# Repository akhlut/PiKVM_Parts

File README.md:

# PiKVM_Parts

Parts I've made for the PiKVM Project.  https://github.com/pikvm/pikvm

All parts are UNTESTED as of 9/23/2020

The idea behind this is to extend the core PiKVM and turn it into a 4-port switch.  4-Port HDMI switches are ubiquitous and inexpensive, making them a less than ideal candidate for designing a PCB around.  Given that GPIO pins can be assigned to specific functions it only makes sense to start building out a 4-port USB/ATX controller built on top of PiKVM.  Couple this with a way to mimic a button-press on an HDMI switch and we're in business.  

The USB and ATX PCB's stack on top of one another, minimizing the footprint.  The PCB's extend the width of the Pi, but not the length.  At some point I'll have to design a case.

Everything is drawn in EAGLE as it's the tool that I'm used to.

Questions?  
Ask on the discord server:  https://discord.com/channels/580094191938437144

Ask on the subreddit: https://old.reddit.com/r/pikvm/

Happy soldering!

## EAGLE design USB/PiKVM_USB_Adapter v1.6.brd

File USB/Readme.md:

PiKVM USB splitter design notes

AS OF 09232020 THIS DESIGN IS COMPLETE BUT UNTESTED!!!

This design uses Analog Devices ADUM3160 iCouplers to provide galvanic isolation between the OTG USB and the (4) external USB ports.

The GPIO pinout (v1.6) is as follows:

PORT A

    GPIO 17

PORT B

    GPIO 24

PORT C

    GPIO 11

PORT D

    GPIO 13

The OTG port can be switched to Ports A-D by holding GPIO HIGH.  

The OTG port does NOT supply power to the Raspberry Pi!  

Power the Pi by either: 

(1) Use the POWER-IN Port on the PCB to supply 5V to the PCB and Pi via the GPIO header

OR

(2) Use a POE hat to power the PI and use jumper cables to power the PCB @ AUX_PWR header

NEVER USE BOTH POWER OPTIONS AT ONCE!

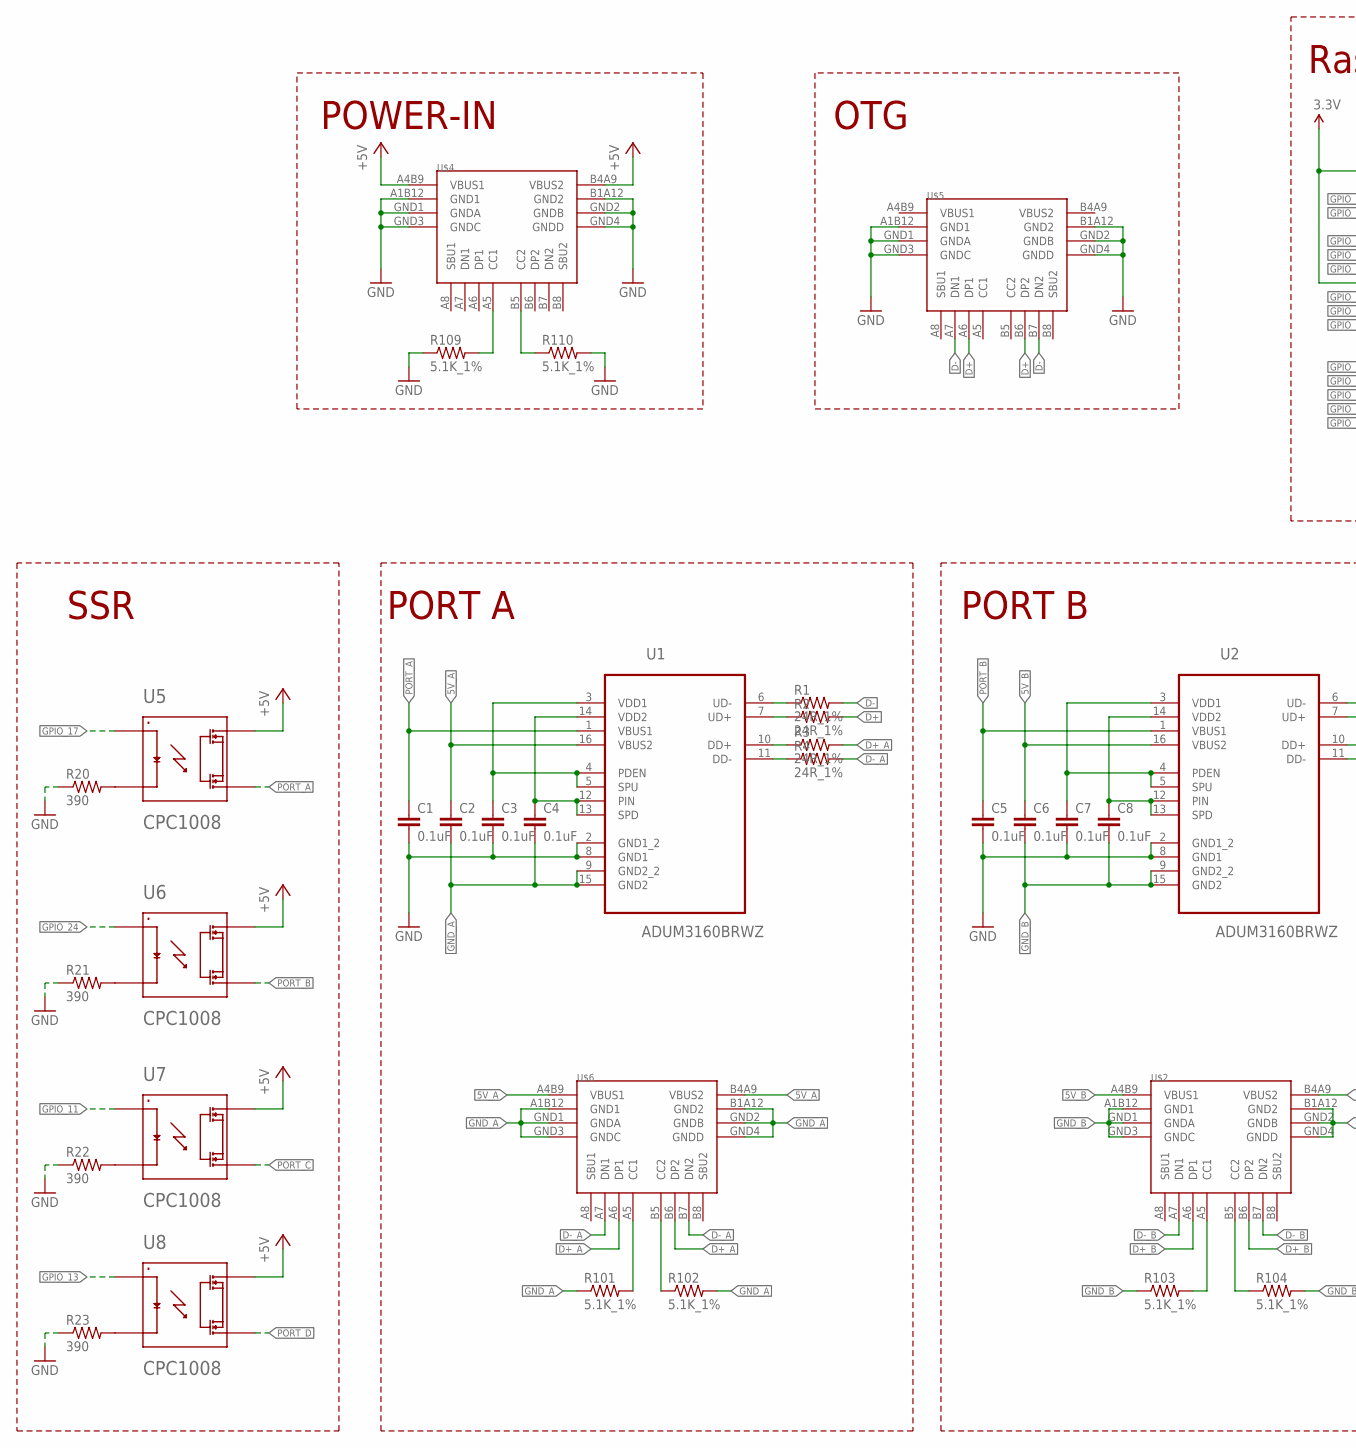
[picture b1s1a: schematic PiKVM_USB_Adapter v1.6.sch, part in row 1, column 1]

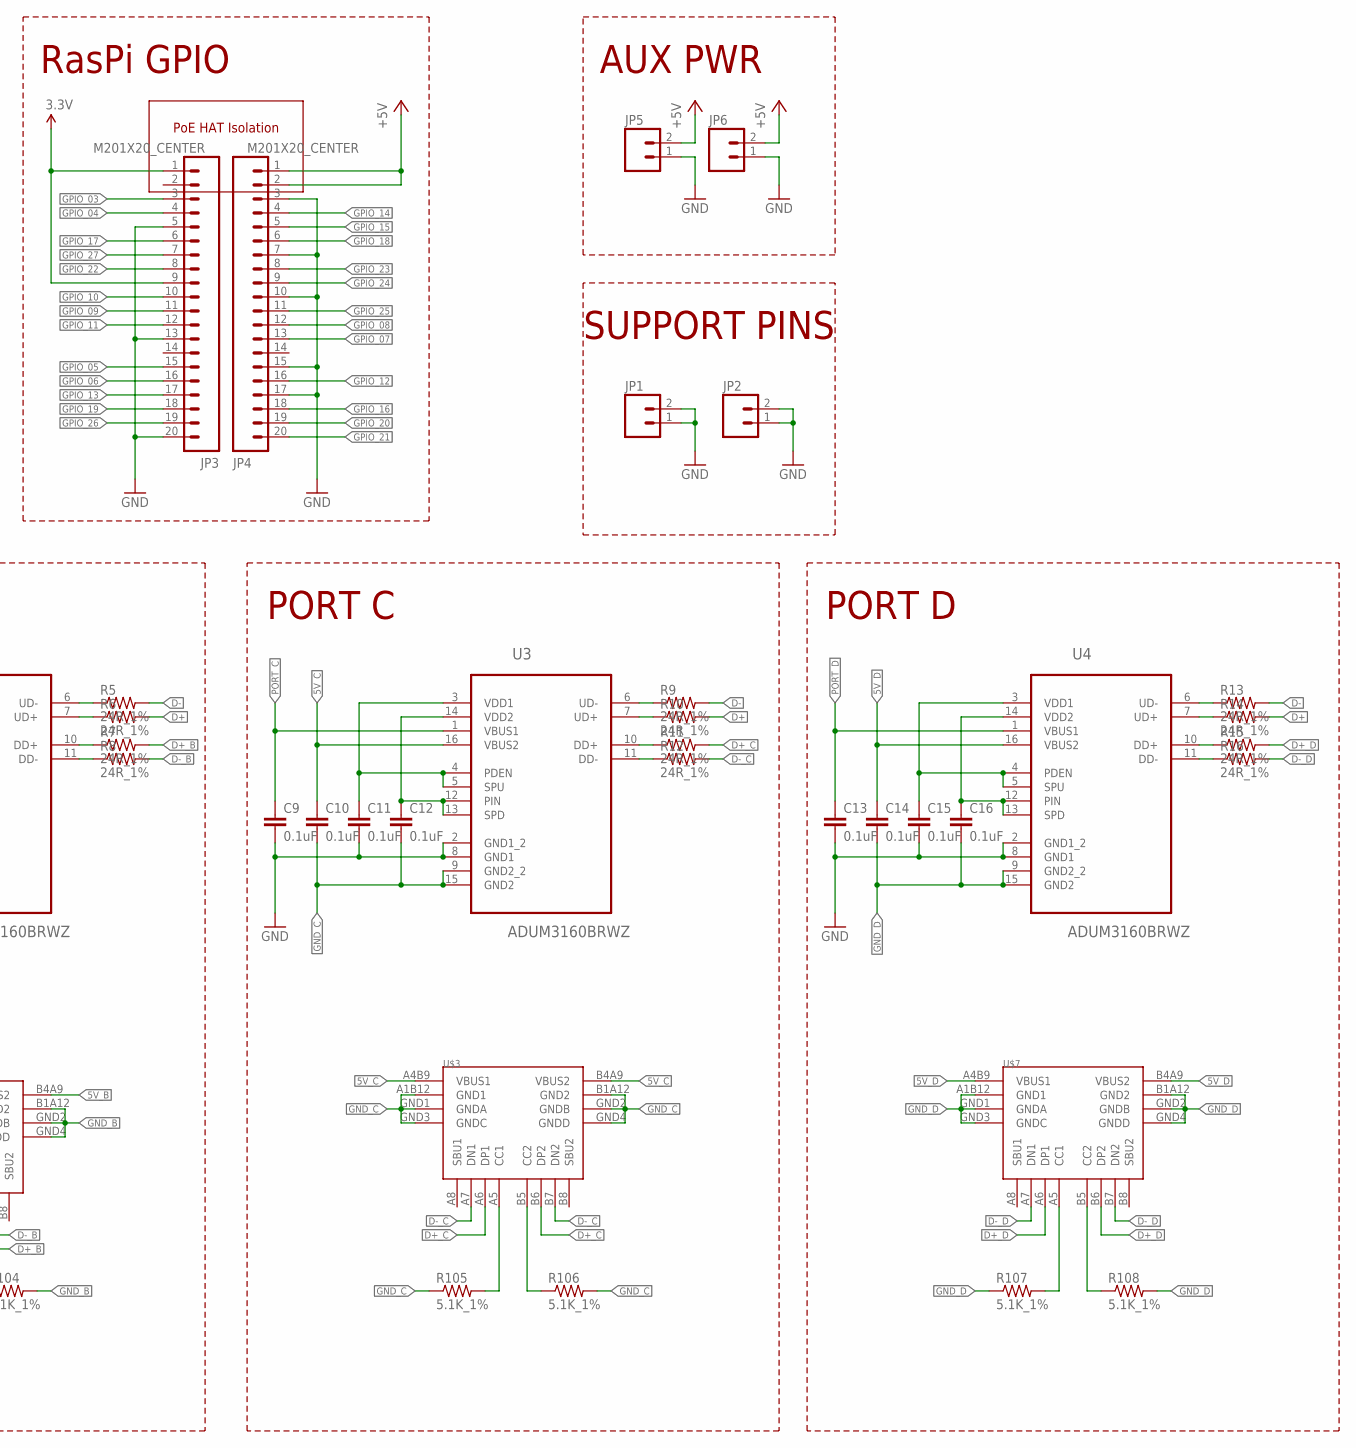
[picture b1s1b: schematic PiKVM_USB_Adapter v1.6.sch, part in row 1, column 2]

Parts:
C1, C2, C3, C4, C5, C6, C7, C8, C9, C10, C11, C12, C13, C14, C15, C16: 0.1uF; 0805
JP1, JP2, JP5, JP6: M02LOCK; 1X02_LOCK
JP3, JP4: M201X20_CENTER; 1X20_CENTER
R1, R2, R3, R4, R5, R6, R7, R8, R9, R10, R11, R12, R13, R14, R15, R16: 24R_1%; 0805
R20, R21, R22, R23: 390; 1206
R101, R102, R103, R104, R105, R106, R107, R108, R109, R110: 5.1K_1%; 0805
U1, U2, U3, U4: ADUM3160BRWZ; SOIC127P1032X265-16N
U5, U6, U7, U8: CPC1008; SOP-4
U$2, U$3, U$4, U$5, U$6, U$7: USB4110GFA; GCT_USB4110GFA

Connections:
3.3V: JP3.1, JP3.9
5V_A: C2.1, U1.16 (VBUS2), U$6.A4B9 (VBUS1), U$6.B4A9 (VBUS2)
5V_B: C6.1, U2.16 (VBUS2), U$2.A4B9 (VBUS1), U$2.B4A9 (VBUS2)
5V_C: C10.1, U3.16 (VBUS2), U$3.A4B9 (VBUS1), U$3.B4A9 (VBUS2)
5V_D: C14.1, U4.16 (VBUS2), U$7.A4B9 (VBUS1), U$7.B4A9 (VBUS2)
+5V: JP4.1, JP4.2, JP5.2, JP6.2, U5.P$4 (4), U6.P$4 (4), U7.P$4 (4), U8.P$4 (4), U$4.A4B9 (VBUS1), U$4.B4A9 (VBUS2)
D+: R2.2, R6.2, R10.2, R14.2, U$5.A6 (DP1), U$5.B6 (DP2)
D+_A: R3.2, U$6.A6 (DP1), U$6.B6 (DP2)
D+_B: R7.2, U$2.A6 (DP1), U$2.B6 (DP2)
D+_C: R11.2, U$3.A6 (DP1), U$3.B6 (DP2)
D+_D: R15.2, U$7.A6 (DP1), U$7.B6 (DP2)
D-: R1.2, R5.2, R9.2, R13.2, U$5.A7 (DN1), U$5.B7 (DN2)
D-_A: R4.2, U$6.A7 (DN1), U$6.B7 (DN2)
D-_B: R8.2, U$2.A7 (DN1), U$2.B7 (DN2)
D-_C: R12.2, U$3.A7 (DN1), U$3.B7 (DN2)
D-_D: R16.2, U$7.A7 (DN1), U$7.B7 (DN2)
GND: C1.2, C3.2, C5.2, C7.2, C9.2, C11.2, C13.2, C15.2, JP1.1, JP1.2, JP2.1, JP2.2, JP3.5, JP3.13, JP3.20, JP4.3, JP4.7, JP4.10, JP4.15, JP4.17, JP5.1, JP6.1, R20.1, R21.1, R22.1, R23.1, R109.1, R110.2, U1.2 (GND1_2), U1.8 (GND1), U2.2 (GND1_2), U2.8 (GND1), U3.2 (GND1_2), U3.8 (GND1), U4.2 (GND1_2), U4.8 (GND1), U$4.A1B12 (GND1), U$4.B1A12 (GND2), U$4.GND1 (GNDA), U$4.GND2 (GNDB), U$4.GND3 (GNDC), U$4.GND4 (GNDD), U$5.A1B12 (GND1), U$5.B1A12 (GND2), U$5.GND1 (GNDA), U$5.GND2 (GNDB), U$5.GND3 (GNDC), U$5.GND4 (GNDD)
GND_A: C2.2, C4.2, R101.1, R102.2, U1.9 (GND2_2), U1.15 (GND2), U$6.A1B12 (GND1), U$6.B1A12 (GND2), U$6.GND1 (GNDA), U$6.GND2 (GNDB), U$6.GND3 (GNDC), U$6.GND4 (GNDD)
GND_B: C6.2, C8.2, R103.1, R104.2, U2.9 (GND2_2), U2.15 (GND2), U$2.A1B12 (GND1), U$2.B1A12 (GND2), U$2.GND1 (GNDA), U$2.GND2 (GNDB), U$2.GND3 (GNDC), U$2.GND4 (GNDD)
GND_C: C10.2, C12.2, R105.1, R106.2, U3.9 (GND2_2), U3.15 (GND2), U$3.A1B12 (GND1), U$3.B1A12 (GND2), U$3.GND1 (GNDA), U$3.GND2 (GNDB), U$3.GND3 (GNDC), U$3.GND4 (GNDD)
GND_D: C14.2, C16.2, R107.1, R108.2, U4.9 (GND2_2), U4.15 (GND2), U$7.A1B12 (GND1), U$7.B1A12 (GND2), U$7.GND1 (GNDA), U$7.GND2 (GNDB), U$7.GND3 (GNDC), U$7.GND4 (GNDD)
GPIO_03: JP3.3
GPIO_04: JP3.4
GPIO_05: JP3.15
GPIO_06: JP3.16
GPIO_07: JP4.13
GPIO_08: JP4.12
GPIO_09: JP3.11
GPIO_10: JP3.10
GPIO_11: JP3.12, U7.P$1 (1)
GPIO_12: JP4.16
GPIO_13: JP3.17, U8.P$1 (1)
GPIO_14: JP4.4
GPIO_15: JP4.5
GPIO_16: JP4.18
GPIO_17: JP3.6, U5.P$1 (1)
GPIO_18: JP4.6
GPIO_19: JP3.18
GPIO_20: JP4.19
GPIO_21: JP4.20
GPIO_22: JP3.8
GPIO_23: JP4.8
GPIO_24: JP4.9, U6.P$1 (1)
GPIO_25: JP4.11
GPIO_26: JP3.19
GPIO_27: JP3.7
unnamed: C8.1, U2.12 (PIN), U2.13 (SPD), U2.14 (VDD2)
unnamed: R5.1, U2.6 (UD-)
unnamed: R6.1, U2.7 (UD+)
unnamed: R7.1, U2.10 (DD+)
unnamed: R20.2, U5.P$2 (2)
unnamed: R8.1, U2.11 (DD-)
unnamed: C3.1, U1.3 (VDD1), U1.4 (PDEN), U1.5 (SPU)
unnamed: R101.2, U$6.A5 (CC1)
unnamed: C12.1, U3.12 (PIN), U3.13 (SPD), U3.14 (VDD2)
unnamed: R9.1, U3.6 (UD-)
unnamed: R10.1, U3.7 (UD+)
unnamed: R11.1, U3.10 (DD+)
unnamed: R12.1, U3.11 (DD-)
unnamed: R102.1, U$6.B5 (CC2)
unnamed: R108.1, U$7.B5 (CC2)
unnamed: C16.1, U4.12 (PIN), U4.13 (SPD), U4.14 (VDD2)
unnamed: R13.1, U4.6 (UD-)
unnamed: R107.2, U$7.A5 (CC1)
unnamed: C4.1, U1.12 (PIN), U1.13 (SPD), U1.14 (VDD2)
unnamed: R14.1, U4.7 (UD+)
unnamed: R15.1, U4.10 (DD+)
unnamed: R16.1, U4.11 (DD-)
unnamed: R1.1, U1.6 (UD-)
unnamed: R2.1, U1.7 (UD+)
unnamed: R3.1, U1.10 (DD+)
unnamed: R4.1, U1.11 (DD-)
unnamed: R105.2, U$3.A5 (CC1)
unnamed: R106.1, U$3.B5 (CC2)
unnamed: R21.2, U6.P$2 (2)
unnamed: R22.2, U7.P$2 (2)
unnamed: R23.2, U8.P$2 (2)
unnamed: C7.1, U2.3 (VDD1), U2.4 (PDEN), U2.5 (SPU)
unnamed: R104.1, U$2.B5 (CC2)
unnamed: C11.1, U3.3 (VDD1), U3.4 (PDEN), U3.5 (SPU)
unnamed: C15.1, U4.3 (VDD1), U4.4 (PDEN), U4.5 (SPU)
unnamed: R103.2, U$2.A5 (CC1)
unnamed: R109.2, U$4.A5 (CC1)
unnamed: R110.1, U$4.B5 (CC2)
PORT_A: C1.1, U1.1 (VBUS1), U5.P$3 (3)
PORT_B: C5.1, U2.1 (VBUS1), U6.P$3 (3)
PORT_C: C9.1, U3.1 (VBUS1), U7.P$3 (3)
PORT_D: C13.1, U4.1 (VBUS1), U8.P$3 (3)
VBUS1: U$5.A4B9 (VBUS1)
VBUS2: U$5.B4A9 (VBUS2)

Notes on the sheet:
PoE HAT Isolation
PORT A
PORT B
PORT C
PORT D
SSR
RasPi GPIO
OTG
POWER-IN
AUX PWR
SUPPORT PINS

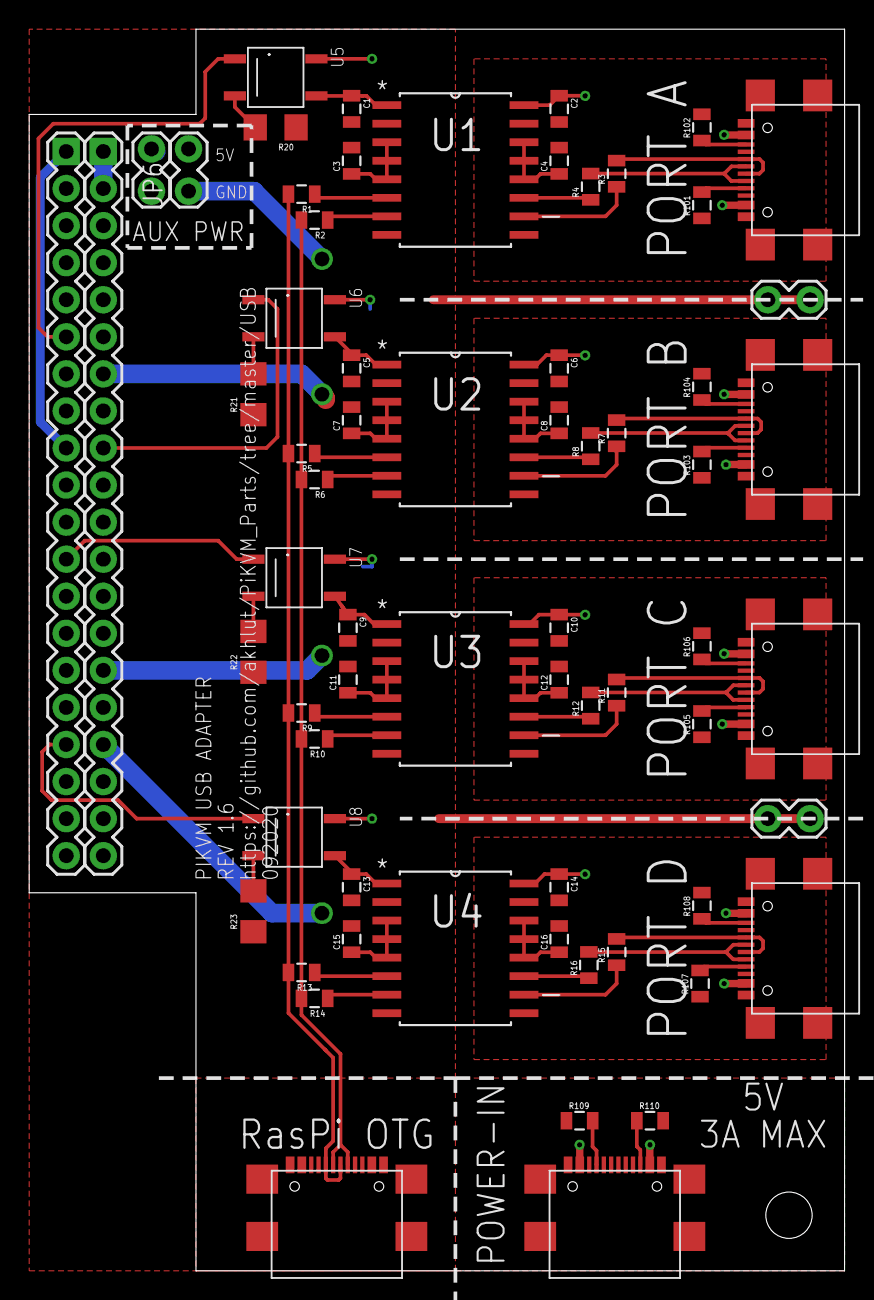
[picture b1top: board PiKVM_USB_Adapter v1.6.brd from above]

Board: 2 copper layers, 55.9 x 85.1 mm, 66 parts (0 on the bottom side), 67 nets.

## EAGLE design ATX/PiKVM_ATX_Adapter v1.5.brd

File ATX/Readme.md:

PiKVM ATX controller design notes

This design uses RJ45 connectors as they are cheap, compact, and ubiquitous.

The RJ45 pinout (v1.5) uses the T-568B pattern and is as follows:

    PIN_1 : W-O : POWER LED +

    PIN_2 : O-W : POWER LED -

    PIN_3 : W-G : IDE LED -

    PIN_4 : Bl-W : RESET -

    PIN_5 : W-Bl : RESET +

    PIN_6 : G-W : IDE LED +

    PIN_7 : W-Br : POWER +

    PIN_8 : Br-W : POWER -

-----

The GPIO pinout (v1) is as follows:

PORT A

    GPIO 03 - POWER

    GPIO 15 - RESET

    GPIO 04 - POWER LED

    GPIO 14 - IDE LED

PORT B

    GPIO 18 - POWER

    GPIO 27 - RESET

    GPIO 22 - POWER LED

    GPIO 23 - IDE LED

PORT C

    GPIO 10 - POWER

    GPIO 08 - RESET

    GPIO 09 - POWER LED

    GPIO 25 - IDE LED

PORT D

    GPIO 07 - POWER

    GPIO 06 - RESET

    GPIO 12 - POWER LED

    GPIO 05 - IDE LED

---

There is also a port to control an external switch.  A DC barrel jack is provided for connectivity.  There is no polarity, simply Common/Normally Open.  This is useful to control external HDMI/KVM switches.

EXTERNAL CONTROL PORT - GPIO 21

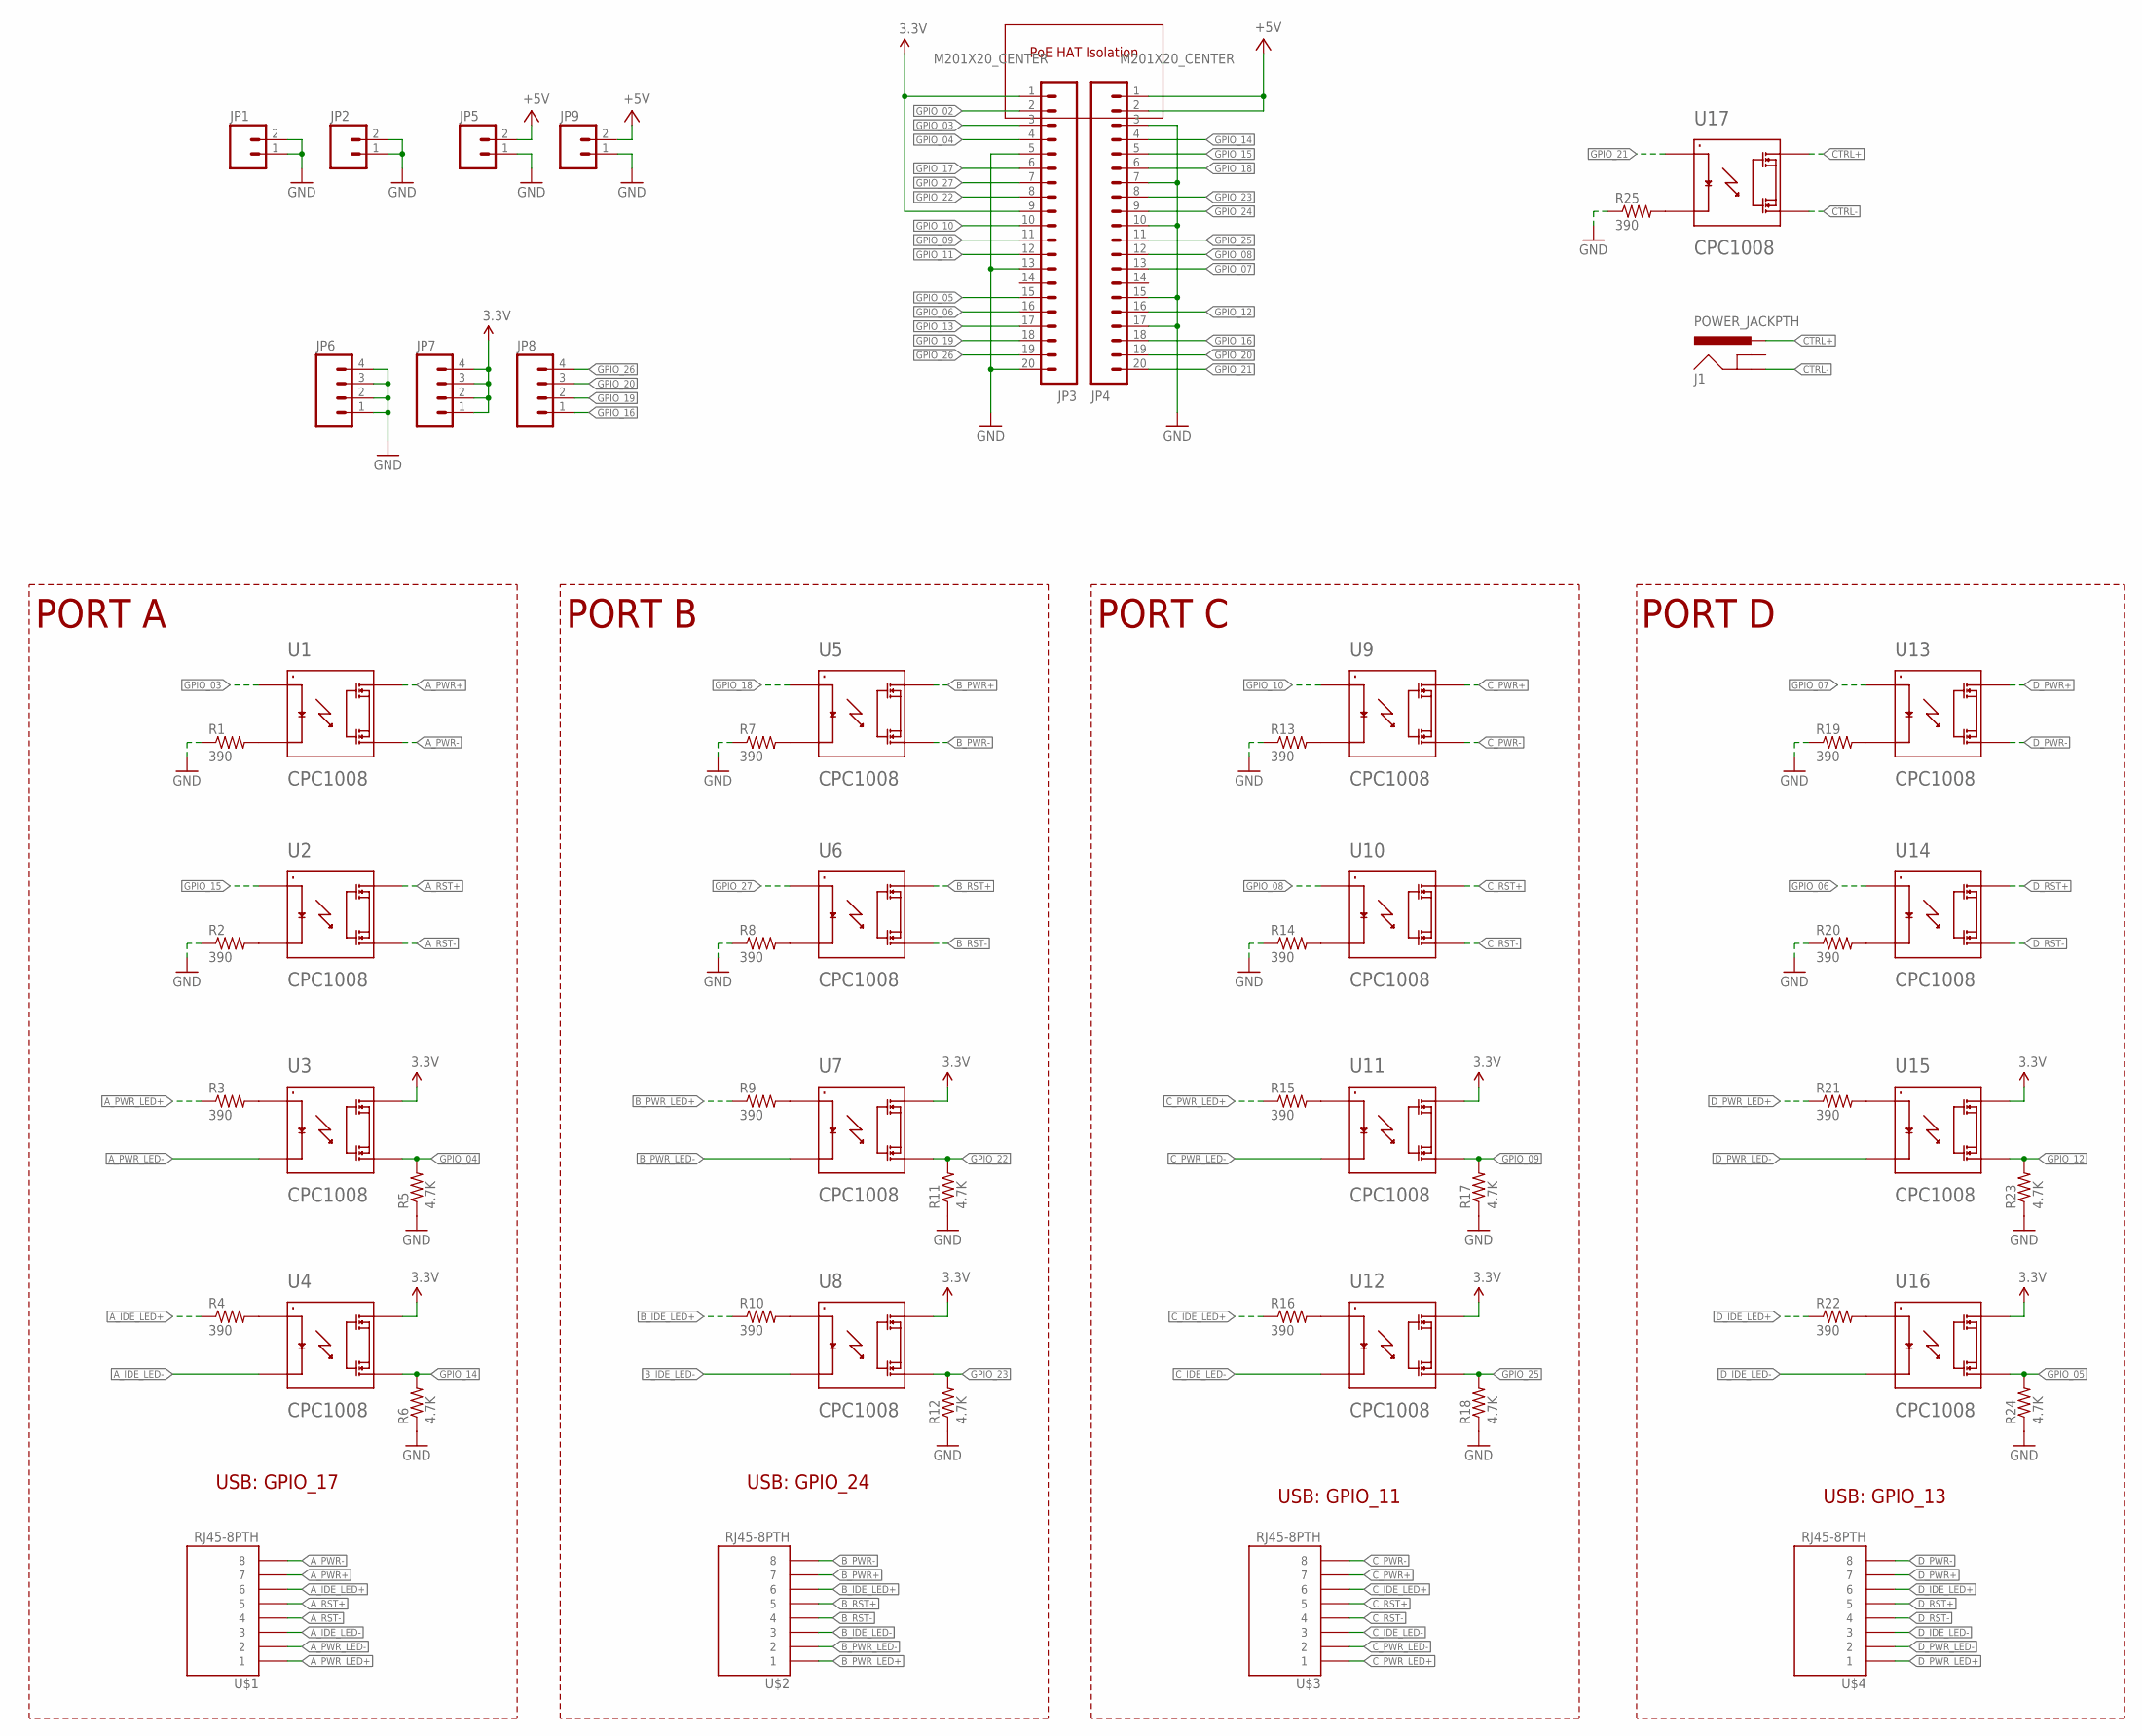
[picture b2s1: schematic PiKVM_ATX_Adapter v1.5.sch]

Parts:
J1: POWER_JACKPTH; POWER_JACK_PTH
JP1, JP2, JP5, JP9: M02LOCK; 1X02_LOCK
JP3, JP4: M201X20_CENTER; 1X20_CENTER
JP6, JP7, JP8: M04PTH; 1X04
R1, R2, R3, R4, R7, R8, R9, R10, R13, R14, R15, R16, R19, R20, R21, R22, R25: 390; 1206
R5, R6, R11, R12, R17, R18, R23, R24: 4.7K; 1206
U1, U2, U3, U4, U5, U6, U7, U8, U9, U10, U11, U12, U13, U14, U15, U16, U17: CPC1008; SOP-4
U$1, U$2, U$3, U$4: RJ45-8PTH; RJ45-8

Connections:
3.3V: JP3.1, JP3.9, JP7.1, JP7.2, JP7.3, JP7.4, U3.P$4 (4), U4.P$4 (4), U7.P$4 (4), U8.P$4 (4), U11.P$4 (4), U12.P$4 (4), U15.P$4 (4), U16.P$4 (4)
+5V: JP4.1, JP4.2, JP5.2, JP9.2
A_IDE_LED+: R4.1, U$1.6
A_IDE_LED-: U4.P$2 (2), U$1.3
A_PWR+: U1.P$4 (4), U$1.7
A_PWR-: U1.P$3 (3), U$1.8
A_PWR_LED+: R3.1, U$1.1
A_PWR_LED-: U3.P$2 (2), U$1.2
A_RST+: U2.P$4 (4), U$1.5
A_RST-: U2.P$3 (3), U$1.4
B_IDE_LED+: R10.1, U$2.6
B_IDE_LED-: U8.P$2 (2), U$2.3
B_PWR+: U5.P$4 (4), U$2.7
B_PWR-: U5.P$3 (3), U$2.8
B_PWR_LED+: R9.1, U$2.1
B_PWR_LED-: U7.P$2 (2), U$2.2
B_RST+: U6.P$4 (4), U$2.5
B_RST-: U6.P$3 (3), U$2.4
CTRL+: J1.PWR, U17.P$4 (4)
CTRL-: J1.GND, U17.P$3 (3)
C_IDE_LED+: R16.1, U$3.6
C_IDE_LED-: U12.P$2 (2), U$3.3
C_PWR+: U9.P$4 (4), U$3.7
C_PWR-: U9.P$3 (3), U$3.8
C_PWR_LED+: R15.1, U$3.1
C_PWR_LED-: U11.P$2 (2), U$3.2
C_RST+: U10.P$4 (4), U$3.5
C_RST-: U10.P$3 (3), U$3.4
D_IDE_LED+: R22.1, U$4.6
D_IDE_LED-: U16.P$2 (2), U$4.3
D_PWR+: U13.P$4 (4), U$4.7
D_PWR-: U13.P$3 (3), U$4.8
D_PWR_LED+: R21.1, U$4.1
D_PWR_LED-: U15.P$2 (2), U$4.2
D_RST+: U14.P$4 (4), U$4.5
D_RST-: U14.P$3 (3), U$4.4
GND: JP1.1, JP1.2, JP2.1, JP2.2, JP3.5, JP3.13, JP3.20, JP4.3, JP4.7, JP4.10, JP4.15, JP4.17, JP5.1, JP6.1, JP6.2, JP6.3, JP6.4, JP9.1, R1.1, R2.1, R5.1, R6.1, R7.1, R8.1, R11.1, R12.1, R13.1, R14.1, R17.1, R18.1, R19.1, R20.1, R23.1, R24.1, R25.1
GPIO_02: JP3.2
GPIO_03: JP3.3, U1.P$1 (1)
GPIO_04: JP3.4, R5.2, U3.P$3 (3)
GPIO_05: JP3.15, R24.2, U16.P$3 (3)
GPIO_06: JP3.16, U14.P$1 (1)
GPIO_07: JP4.13, U13.P$1 (1)
GPIO_08: JP4.12, U10.P$1 (1)
GPIO_09: JP3.11, R17.2, U11.P$3 (3)
GPIO_10: JP3.10, U9.P$1 (1)
GPIO_11: JP3.12
GPIO_12: JP4.16, R23.2, U15.P$3 (3)
GPIO_13: JP3.17
GPIO_14: JP4.4, R6.2, U4.P$3 (3)
GPIO_15: JP4.5, U2.P$1 (1)
GPIO_16: JP4.18, JP8.1
GPIO_17: JP3.6
GPIO_18: JP4.6, U5.P$1 (1)
GPIO_19: JP3.18, JP8.2
GPIO_20: JP4.19, JP8.3
GPIO_21: JP4.20, U17.P$1 (1)
GPIO_22: JP3.8, R11.2, U7.P$3 (3)
GPIO_23: JP4.8, R12.2, U8.P$3 (3)
GPIO_24: JP4.9
GPIO_25: JP4.11, R18.2, U12.P$3 (3)
GPIO_26: JP3.19, JP8.4
GPIO_27: JP3.7, U6.P$1 (1)
unnamed: R2.2, U2.P$2 (2)
unnamed: R3.2, U3.P$1 (1)
unnamed: R7.2, U5.P$2 (2)
unnamed: R1.2, U1.P$2 (2)
unnamed: R4.2, U4.P$1 (1)
unnamed: R8.2, U6.P$2 (2)
unnamed: R9.2, U7.P$1 (1)
unnamed: R10.2, U8.P$1 (1)
unnamed: R13.2, U9.P$2 (2)
unnamed: R14.2, U10.P$2 (2)
unnamed: R15.2, U11.P$1 (1)
unnamed: R16.2, U12.P$1 (1)
unnamed: R19.2, U13.P$2 (2)
unnamed: R20.2, U14.P$2 (2)
unnamed: R21.2, U15.P$1 (1)
unnamed: R22.2, U16.P$1 (1)
unnamed: R25.2, U17.P$2 (2)

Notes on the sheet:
PoE HAT Isolation
PORT A
PORT B
PORT C
PORT D
USB: GPIO_17
USB: GPIO_24
USB: GPIO_11
USB: GPIO_13

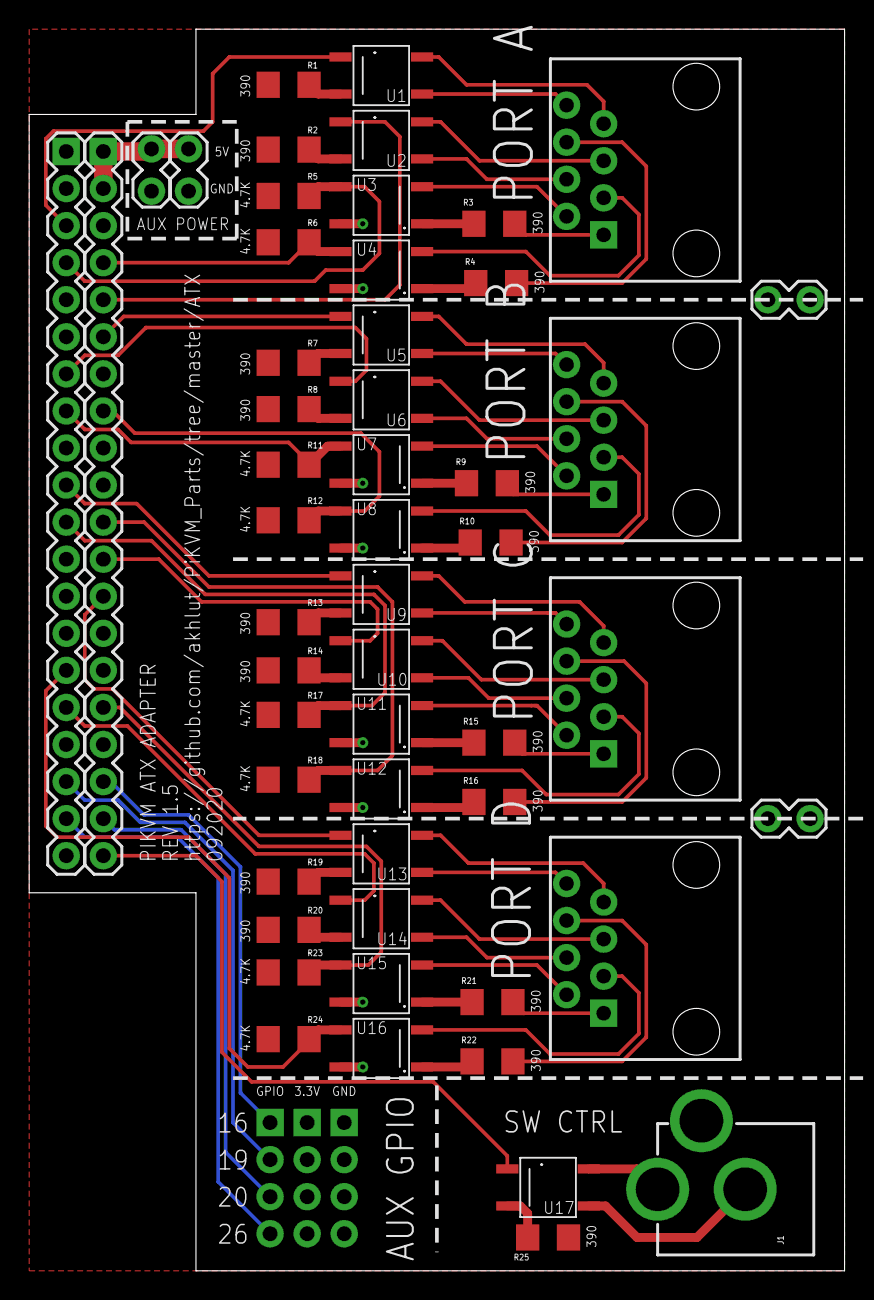
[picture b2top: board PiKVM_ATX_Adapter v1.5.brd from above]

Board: 2 copper layers, 55.9 x 85.1 mm, 56 parts (0 on the bottom side), 75 nets.

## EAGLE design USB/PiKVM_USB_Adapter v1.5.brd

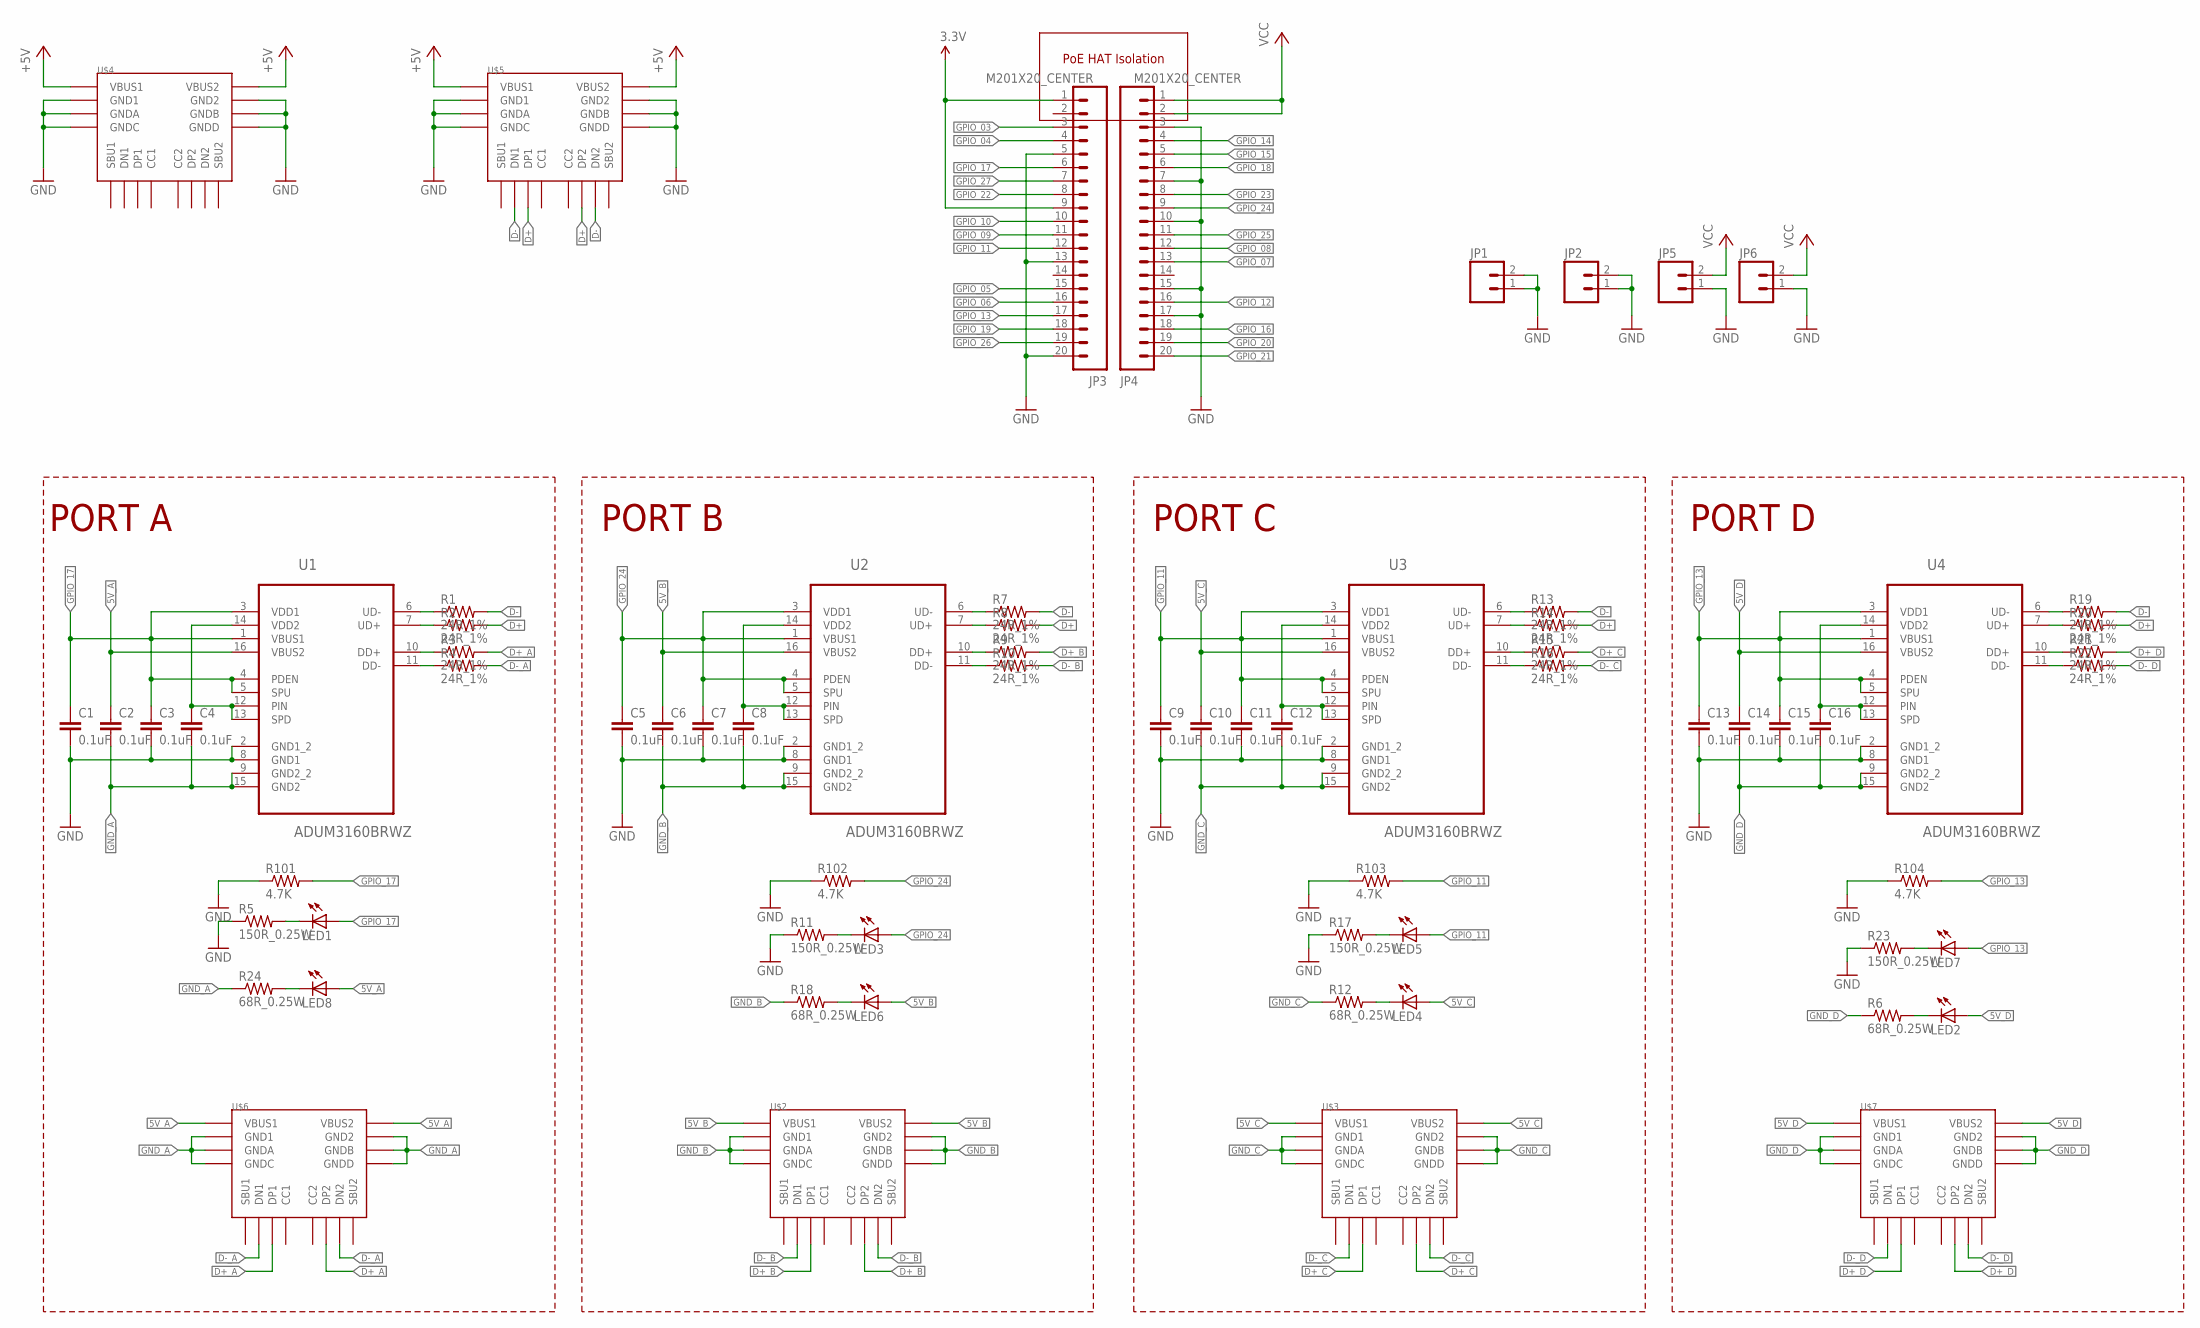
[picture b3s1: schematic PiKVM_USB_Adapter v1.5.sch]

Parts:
C1, C2, C3, C4, C5, C6, C7, C8, C9, C10, C11, C12, C13, C14, C15, C16: 0.1uF; 0805
JP1, JP2, JP5, JP6: M02LOCK; 1X02_LOCK
JP3, JP4: M201X20_CENTER; 1X20_CENTER
LED1, LED2, LED3, LED4, LED5, LED6, LED7, LED8: LED1206; LED-1206
R1, R2, R3, R4, R7, R8, R9, R10, R13, R14, R15, R16, R19, R20, R21, R22: 24R_1%; 0805
R5, R11, R17, R23: 150R_0.25W; 1206
R6, R12, R18, R24: 68R_0.25W; 1206
R101, R102, R103, R104: 4.7K; 1206
U1, U2, U3, U4: ADUM3160BRWZ; SOIC127P1032X265-16N
U$2, U$3, U$4, U$5, U$6, U$7: USB4110GFA; GCT_USB4110GFA

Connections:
3.3V: JP3.1, JP3.9
5V_A: C2.1, LED8.A, U1.16 (VBUS2), U$6.A4B9 (VBUS1), U$6.B4A9 (VBUS2)
5V_B: C6.1, LED6.A, U2.16 (VBUS2), U$2.A4B9 (VBUS1), U$2.B4A9 (VBUS2)
5V_C: C10.1, LED4.A, U3.16 (VBUS2), U$3.A4B9 (VBUS1), U$3.B4A9 (VBUS2)
5V_D: C14.1, LED2.A, U4.16 (VBUS2), U$7.A4B9 (VBUS1), U$7.B4A9 (VBUS2)
+5V: U$4.A4B9 (VBUS1), U$4.B4A9 (VBUS2), U$5.A4B9 (VBUS1), U$5.B4A9 (VBUS2)
D+: R2.2, R8.2, R14.2, R20.2, U$5.A6 (DP1), U$5.B6 (DP2)
D+_A: R3.2, U$6.A6 (DP1), U$6.B6 (DP2)
D+_B: R9.2, U$2.A6 (DP1), U$2.B6 (DP2)
D+_C: R15.2, U$3.A6 (DP1), U$3.B6 (DP2)
D+_D: R21.2, U$7.A6 (DP1), U$7.B6 (DP2)
D-: R1.2, R7.2, R13.2, R19.2, U$5.A7 (DN1), U$5.B7 (DN2)
D-_A: R4.2, U$6.A7 (DN1), U$6.B7 (DN2)
D-_B: R10.2, U$2.A7 (DN1), U$2.B7 (DN2)
D-_C: R16.2, U$3.A7 (DN1), U$3.B7 (DN2)
D-_D: R22.2, U$7.A7 (DN1), U$7.B7 (DN2)
GND: C1.2, C3.2, C5.2, C7.2, C9.2, C11.2, C13.2, C15.2, JP1.1, JP1.2, JP2.1, JP2.2, JP3.5, JP3.13, JP3.20, JP4.3, JP4.7, JP4.10, JP4.15, JP4.17, JP5.1, JP6.1, R5.1, R11.1, R17.1, R23.1, R101.1, R102.1, R103.1, R104.1, U1.2 (GND1_2), U1.8 (GND1), U2.2 (GND1_2), U2.8 (GND1), U3.2 (GND1_2), U3.8 (GND1), U4.2 (GND1_2), U4.8 (GND1), U$4.A1B12 (GND1), U$4.B1A12 (GND2), U$4.GND1 (GNDA), U$4.GND2 (GNDB), U$4.GND3 (GNDC), U$4.GND4 (GNDD), U$5.A1B12 (GND1), U$5.B1A12 (GND2), U$5.GND1 (GNDA), U$5.GND2 (GNDB), U$5.GND3 (GNDC), U$5.GND4 (GNDD)
GND_A: C2.2, C4.2, R24.1, U1.9 (GND2_2), U1.15 (GND2), U$6.A1B12 (GND1), U$6.B1A12 (GND2), U$6.GND1 (GNDA), U$6.GND2 (GNDB), U$6.GND3 (GNDC), U$6.GND4 (GNDD)
GND_B: C6.2, C8.2, R18.1, U2.9 (GND2_2), U2.15 (GND2), U$2.A1B12 (GND1), U$2.B1A12 (GND2), U$2.GND1 (GNDA), U$2.GND2 (GNDB), U$2.GND3 (GNDC), U$2.GND4 (GNDD)
GND_C: C10.2, C12.2, R12.1, U3.9 (GND2_2), U3.15 (GND2), U$3.A1B12 (GND1), U$3.B1A12 (GND2), U$3.GND1 (GNDA), U$3.GND2 (GNDB), U$3.GND3 (GNDC), U$3.GND4 (GNDD)
GND_D: C14.2, C16.2, R6.1, U4.9 (GND2_2), U4.15 (GND2), U$7.A1B12 (GND1), U$7.B1A12 (GND2), U$7.GND1 (GNDA), U$7.GND2 (GNDB), U$7.GND3 (GNDC), U$7.GND4 (GNDD)
GPIO_03: JP3.3
GPIO_04: JP3.4
GPIO_05: JP3.15
GPIO_06: JP3.16
GPIO_07: JP4.13
GPIO_08: JP4.12
GPIO_09: JP3.11
GPIO_10: JP3.10
GPIO_11: C9.1, C11.1, JP3.12, LED5.A, R103.2, U3.1 (VBUS1), U3.3 (VDD1), U3.4 (PDEN), U3.5 (SPU)
GPIO_12: JP4.16
GPIO_13: C13.1, C15.1, JP3.17, LED7.A, R104.2, U4.1 (VBUS1), U4.3 (VDD1), U4.4 (PDEN), U4.5 (SPU)
GPIO_14: JP4.4
GPIO_15: JP4.5
GPIO_16: JP4.18
GPIO_17: C1.1, C3.1, JP3.6, LED1.A, R101.2, U1.1 (VBUS1), U1.3 (VDD1), U1.4 (PDEN), U1.5 (SPU)
GPIO_18: JP4.6
GPIO_19: JP3.18
GPIO_20: JP4.19
GPIO_21: JP4.20
GPIO_22: JP3.8
GPIO_23: JP4.8
GPIO_24: C5.1, C7.1, JP4.9, LED3.A, R102.2, U2.1 (VBUS1), U2.3 (VDD1), U2.4 (PDEN), U2.5 (SPU)
GPIO_25: JP4.11
GPIO_26: JP3.19
GPIO_27: JP3.7
unnamed: C8.1, U2.12 (PIN), U2.13 (SPD), U2.14 (VDD2)
unnamed: R7.1, U2.6 (UD-)
unnamed: R8.1, U2.7 (UD+)
unnamed: R9.1, U2.10 (DD+)
unnamed: R10.1, U2.11 (DD-)
unnamed: LED3.C, R11.2
unnamed: C12.1, U3.12 (PIN), U3.13 (SPD), U3.14 (VDD2)
unnamed: R13.1, U3.6 (UD-)
unnamed: R14.1, U3.7 (UD+)
unnamed: R15.1, U3.10 (DD+)
unnamed: R16.1, U3.11 (DD-)
unnamed: LED2.C, R6.2
unnamed: LED5.C, R17.2
unnamed: C16.1, U4.12 (PIN), U4.13 (SPD), U4.14 (VDD2)
unnamed: R19.1, U4.6 (UD-)
unnamed: LED1.C, R5.2
unnamed: C4.1, U1.12 (PIN), U1.13 (SPD), U1.14 (VDD2)
unnamed: R20.1, U4.7 (UD+)
unnamed: R21.1, U4.10 (DD+)
unnamed: R22.1, U4.11 (DD-)
unnamed: R1.1, U1.6 (UD-)
unnamed: R2.1, U1.7 (UD+)
unnamed: R3.1, U1.10 (DD+)
unnamed: R4.1, U1.11 (DD-)
unnamed: LED4.C, R12.2
unnamed: LED7.C, R23.2
unnamed: LED6.C, R18.2
unnamed: LED8.C, R24.2
VCC: JP4.1, JP4.2, JP5.2, JP6.2

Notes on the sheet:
PoE HAT Isolation
PORT A
PORT B
PORT C
PORT D

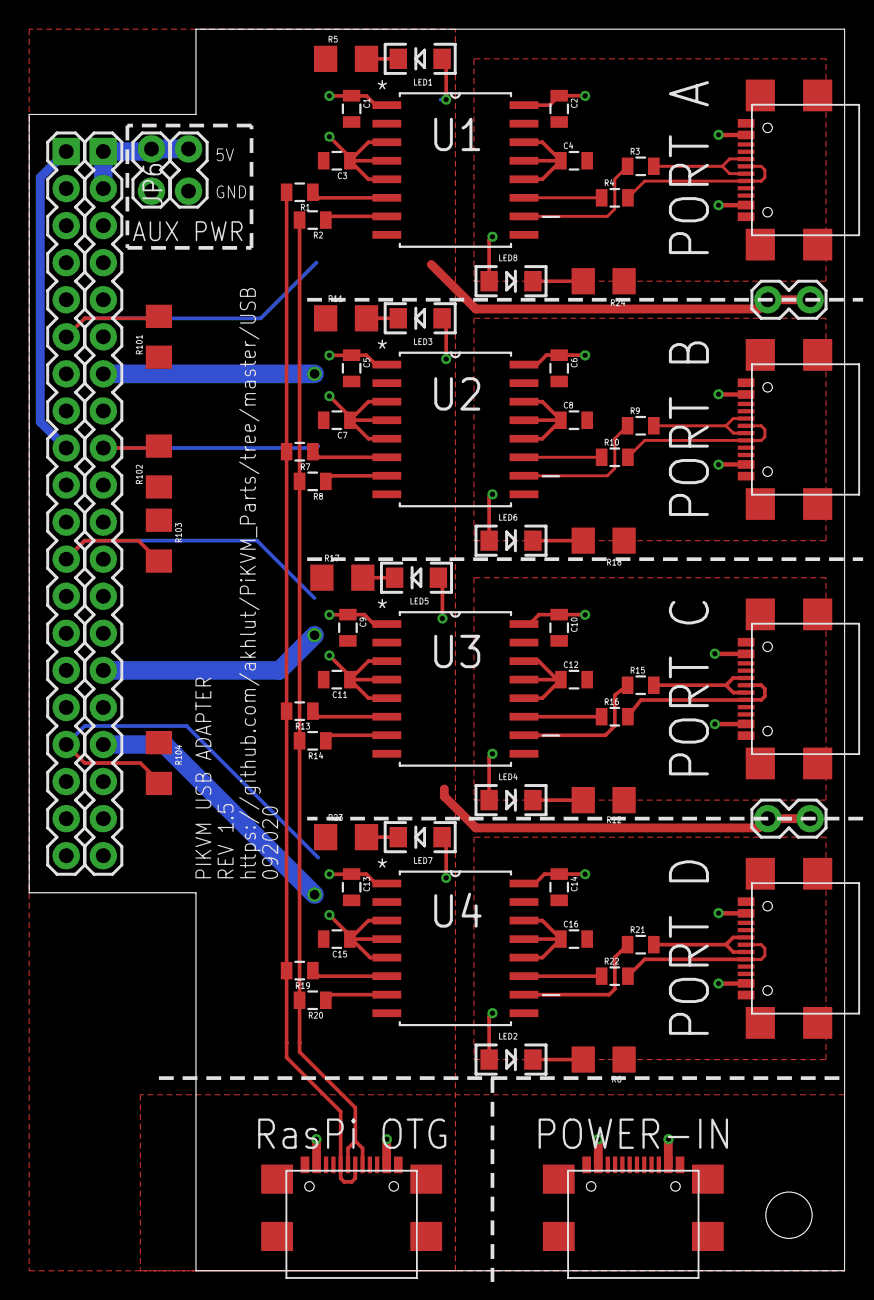
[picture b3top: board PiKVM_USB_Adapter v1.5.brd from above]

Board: 2 copper layers, 55.9 x 85.1 mm, 68 parts (0 on the bottom side), 54 nets.

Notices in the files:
parts and their libraries:
SparkFun-Connectors: Licensing: CC v3.0 Share-Alike You are welcome to use this library for commercial purposes.
